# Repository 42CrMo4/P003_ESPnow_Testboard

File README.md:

# ESPnow Testboard

Quick first shot for an ESP32-C3 based ESPnow communication PCB 

## Description. 

|     Font      |     Back      |
| ------------- | ------------- |
|||

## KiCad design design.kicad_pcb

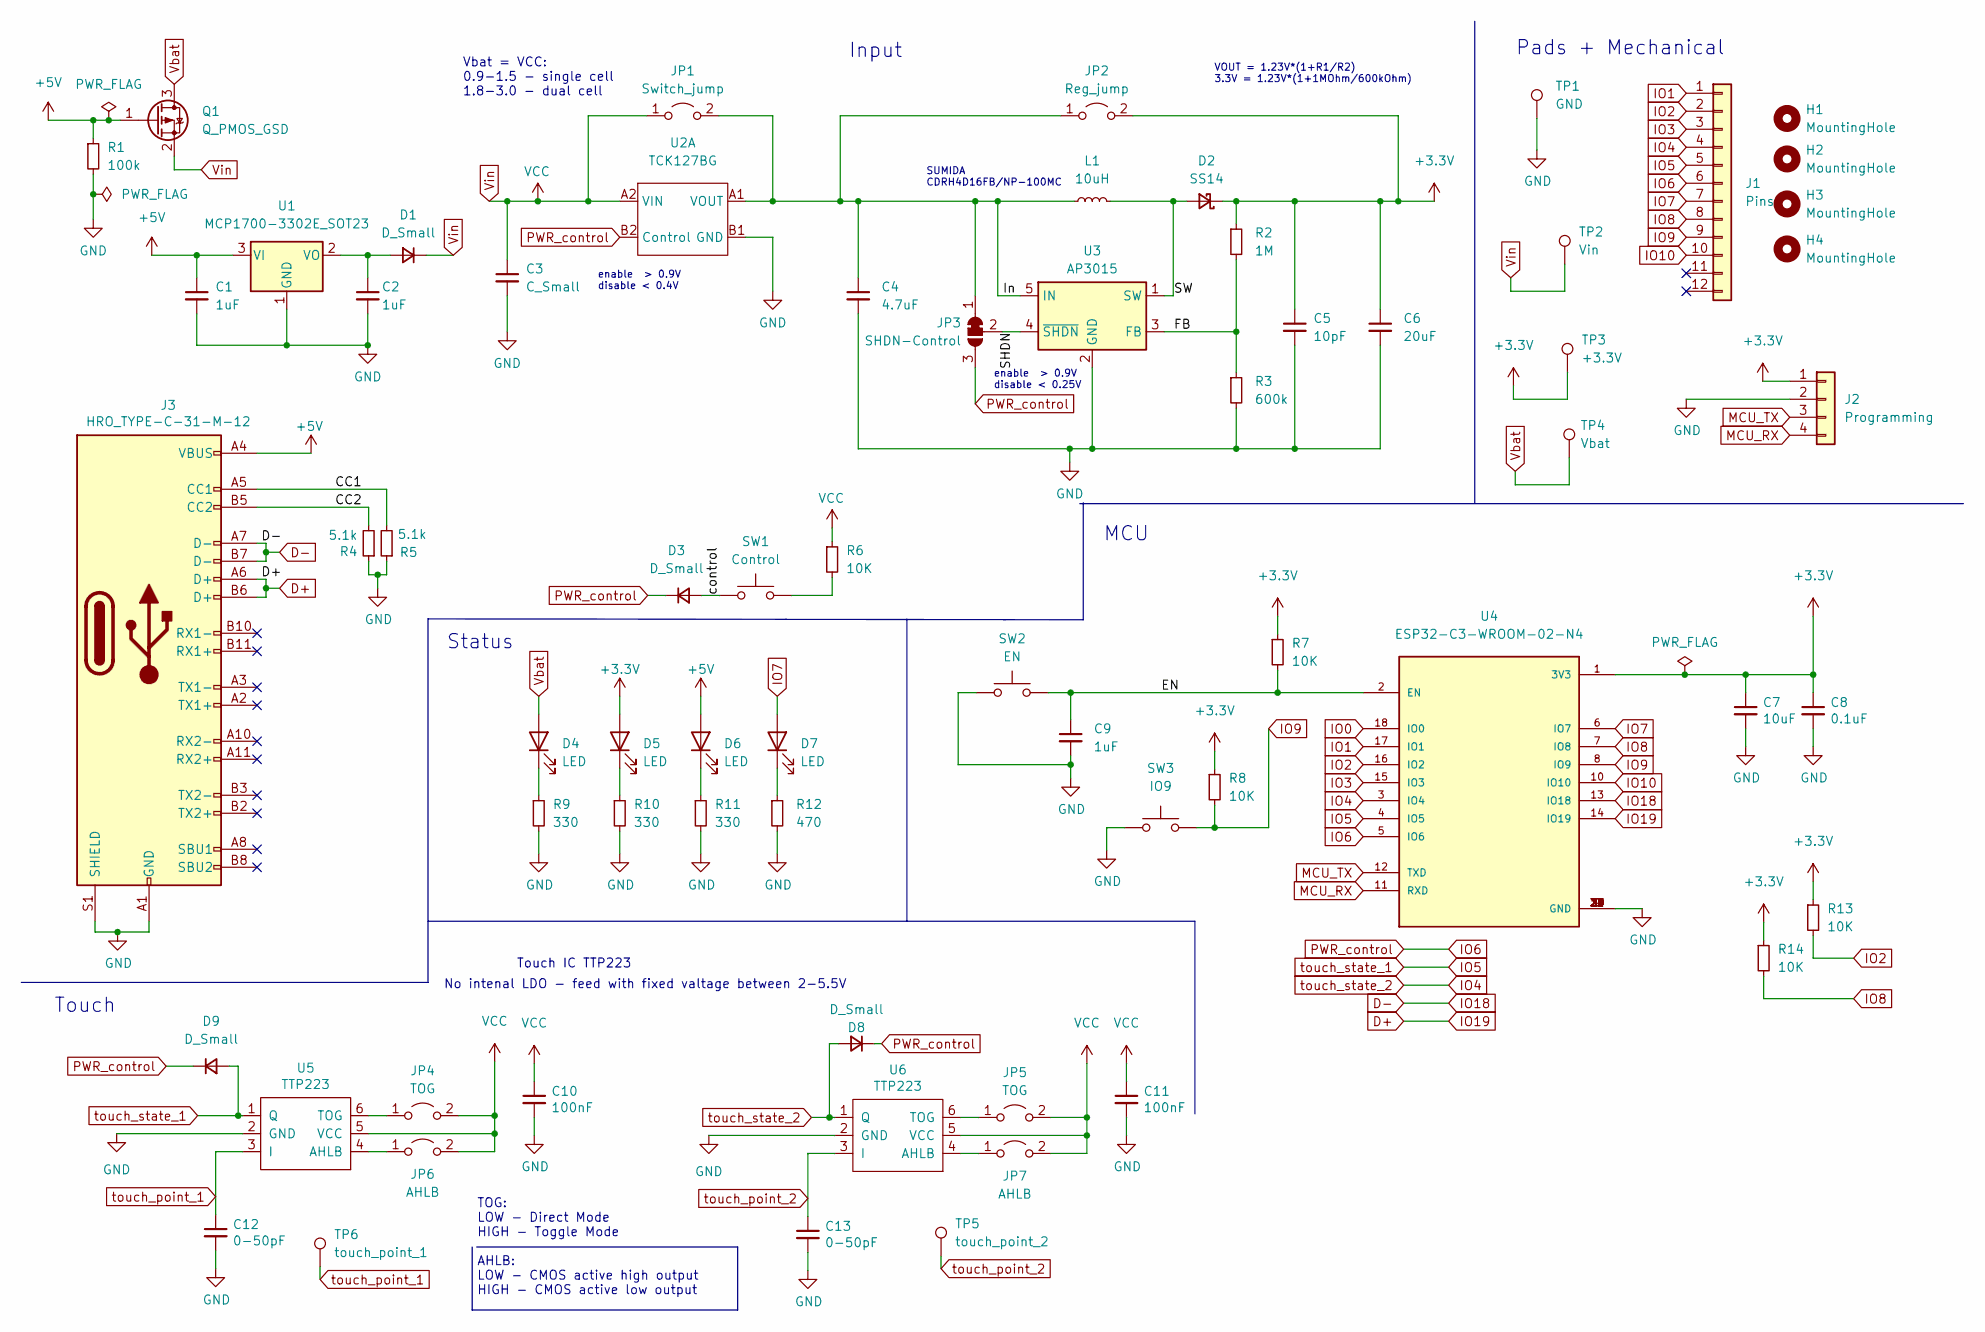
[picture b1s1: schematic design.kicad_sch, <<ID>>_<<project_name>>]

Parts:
C1, C2, C9: 1uF; C_0805_2012Metric
C3: C_Small; C_0805_2012Metric
C4: 4.7uF; C_0805_2012Metric
C5: 10pF; C_0805_2012Metric
C6: 20uF; C_0805_2012Metric
C7: 10uF; C_0805_2012Metric
C8: 0.1uF; C_0805_2012Metric
C10, C11: 100nF; C_0805_2012Metric
C12, C13: 0-50pF; C_0805_2012Metric
D1, D3, D8, D9: D_Small; D_SOD-323
D2: SS14; D_SMA
D4, D5, D6, D7: LED; LED_0603_1608Metric
H1, H2, H3, H4: MountingHole; MountingHole_3.2mm_M3_Pad_Via
J1: Pins; PinSocket_2x06_P2.54mm_Vertical_SMD
J2: Programming; PinHeader_1x04_P2.54mm_Vertical
J3: HRO_TYPE-C-31-M-12; USB_C_Receptacle_HRO_TYPE-C-31-M-12
JP1: Switch_jump; SolderJumper-2_P1.3mm_Open_RoundedPad1.0x1.5mm
JP2: Reg_jump; SolderJumper-2_P1.3mm_Open_RoundedPad1.0x1.5mm
JP3: SHDN-Control; SolderJumper-3_P1.3mm_Bridged12_RoundedPad1.0x1.5mm_NumberL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
JP4, JP5: TOG; SolderJumper-2_P1.3mm_Open_RoundedPad1.0x1.5mm
JP6, JP7: AHLB; SolderJumper-2_P1.3mm_Open_RoundedPad1.0x1.5mm
L1: 10uH; L_TracoPower_TCK-047_5.2x5.8mm
Q1: Q_PMOS_GSD; SOT-23
R1: 100k; R_0805_2012Metric
R2: 1M; R_0805_2012Metric
R3: 600k; R_0805_2012Metric
R4, R5: 5.1k; R_0805_2012Metric
R6, R7, R8, R13, R14: 10K; R_0805_2012Metric
R9, R10, R11: 330; R_0805_2012Metric
R12: 470; R_0805_2012Metric
SW1: Control; SW_SPST_EVPBF
SW2: EN; SW_SPST_EVPBF
SW3: IO9; SW_SPST_EVPBF
TP1: GND; TestPoint_Pad_D2.5mm
TP2: Vin; TestPoint_Pad_D2.5mm
TP3: +3.3V; TestPoint_Pad_D2.5mm
TP4: Vbat; TestPoint_Pad_D2.5mm
TP5: touch_point_2
TP6: touch_point_1
U1: MCP1700-3302E_SOT23; SOT-23
U2: TCK127BG; Toshiba_WCSP4G
U3: AP3015; SOT-23-5
U4: ESP32-C3-WROOM-02-N4; MODULE_ESP32-C3-WROOM-02-H4
U5, U6: TTP223; SOT-23-6_Handsoldering

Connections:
+3.3V: C5.1, C6.1, C7.1, C8.1, D2.1 (K), D5.2 (A), J2.1, JP2.2 (B), R2.1, R7.1, R8.1, R13.1, R14.1, TP3.1, U4.1 (3V3)
+5V: C1.1, D6.2 (A), J3.A4 (VBUS), J3.A9 (VBUS), J3.B4 (VBUS), J3.B9 (VBUS), Q1.1 (G), R1.1, U1.3 (VI)
/CC1: J3.A5 (CC1), R5.2
/CC2: J3.B5 (CC2), R4.2
/EN: C9.1, R7.2, SW2.2, U4.2 (EN)
/FB: R2.2, R3.1, U3.3 (FB)
/In: C4.1, JP1.2 (B), JP2.1 (A), JP3.1 (A), L1.1, U2.A1 (VOUT), U3.5 (IN)
/SHDN: JP3.2 (C), U3.4 (~SHDN)
/SW: D2.2 (A), L1.2, U3.1 (SW)
/control: D3.2 (A), SW1.1
D+: J3.A6 (D+), J3.B6 (D+), U4.14 (IO19)
D-: J3.A7 (D-), J3.B7 (D-), U4.13 (IO18)
GND: C1.2, C2.2, C3.2, C4.2, C5.2, C6.2, C7.2, C8.2, C9.2, C10.2, C11.2, C12.2, C13.2, J2.2, J3.A1 (GND), J3.A12 (GND), J3.B1 (GND), J3.B12 (GND), J3.S1 (SHIELD), R1.2, R3.2, R4.1, R5.1, R9.2, R10.2, R11.2, R12.2, SW2.1, SW3.1, TP1.1, U1.1 (GND), U2.B1 (GND), U3.2 (GND), U4.9 (GND), U4.19 (GND), U4.20 (GND), U4.21 (GND), U4.22 (GND), U4.23 (GND), U4.24 (GND), U4.25 (GND), U4.26 (GND), U4.27 (GND), U4.28 (GND), U4.29 (GND), U4.30 (GND), U4.31 (GND), U4.32 (GND), U4.33 (GND), U4.34 (GND), U4.35 (GND), U4.36 (GND), U4.37 (GND), U4.38 (GND), U4.39 (GND), U5.2 (GND), U6.2 (GND)
IO0: U4.18 (IO0)
IO1: J1.1, U4.17 (IO1)
IO2: J1.2, R13.2, U4.16 (IO2)
IO3: J1.3, U4.15 (IO3)
IO4: D8.2 (A), J1.4, U4.3 (IO4), U6.1 (Q)
IO5: D9.2 (A), J1.5, U4.4 (IO5), U5.1 (Q)
IO6: D3.1 (K), D8.1 (K), D9.1 (K), J1.6, JP3.3 (B), U2.B2 (Control), U4.5 (IO6)
IO7: D7.2 (A), J1.7, U4.6 (IO7)
IO8: J1.8, R14.2, U4.7 (IO8)
IO9: J1.9, R8.2, SW3.2, U4.8 (IO9)
IO10: J1.10, U4.10 (IO10)
MCU_RX: J2.4, U4.11 (RXD)
MCU_TX: J2.3, U4.12 (TXD)
unnamed: C2.1, D1.2 (A), U1.2 (VO)
unnamed: D4.1 (K), R9.1
unnamed: D5.1 (K), R10.1
unnamed: D6.1 (K), R11.1
unnamed: D7.1 (K), R12.1
unnamed: JP4.1 (A), U5.6 (TOG)
unnamed: JP5.1 (A), U6.6 (TOG)
unnamed: JP6.1 (A), U5.4 (AHLB)
unnamed: JP7.1 (A), U6.4 (AHLB)
unnamed: R6.2, SW1.2
Vbat: D4.2 (A), Q1.3 (D), TP4.1
Vin: C3.1, C10.1, C11.1, D1.1 (K), JP1.1 (A), JP4.2 (B), JP5.2 (B), JP6.2 (B), JP7.2 (B), Q1.2 (S), R6.1, TP2.1, U2.A2 (VIN), U5.5 (VCC), U6.5 (VCC)
touch_point_1: C12.1, TP6.1, U5.3 (I)
touch_point_2: C13.1, TP5.1, U6.3 (I)

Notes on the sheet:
enable > 0.9V disable < 0.25V
Pads + Mechanical
enable > 0.9V disable < 0.4V
SUMIDA CDRH4D16FB/NP-100MC
Touch IC TTP223
No intenal LDO - feed with fixed valtage between 2-5.5V
Vbat = VCC: 0.9-1.5 - single cell 1.8-3.0 - dual cell
VOUT = 1.23V*(1+R1/R2) 3.3V = 1.23V*(1+1MOhm/600kOhm)
Status
TOG: LOW - Direct Mode HIGH - Toggle Mode AHLB: LOW - CMOS active high output HIGH - CMOS active low output
Input
Touch
MCU

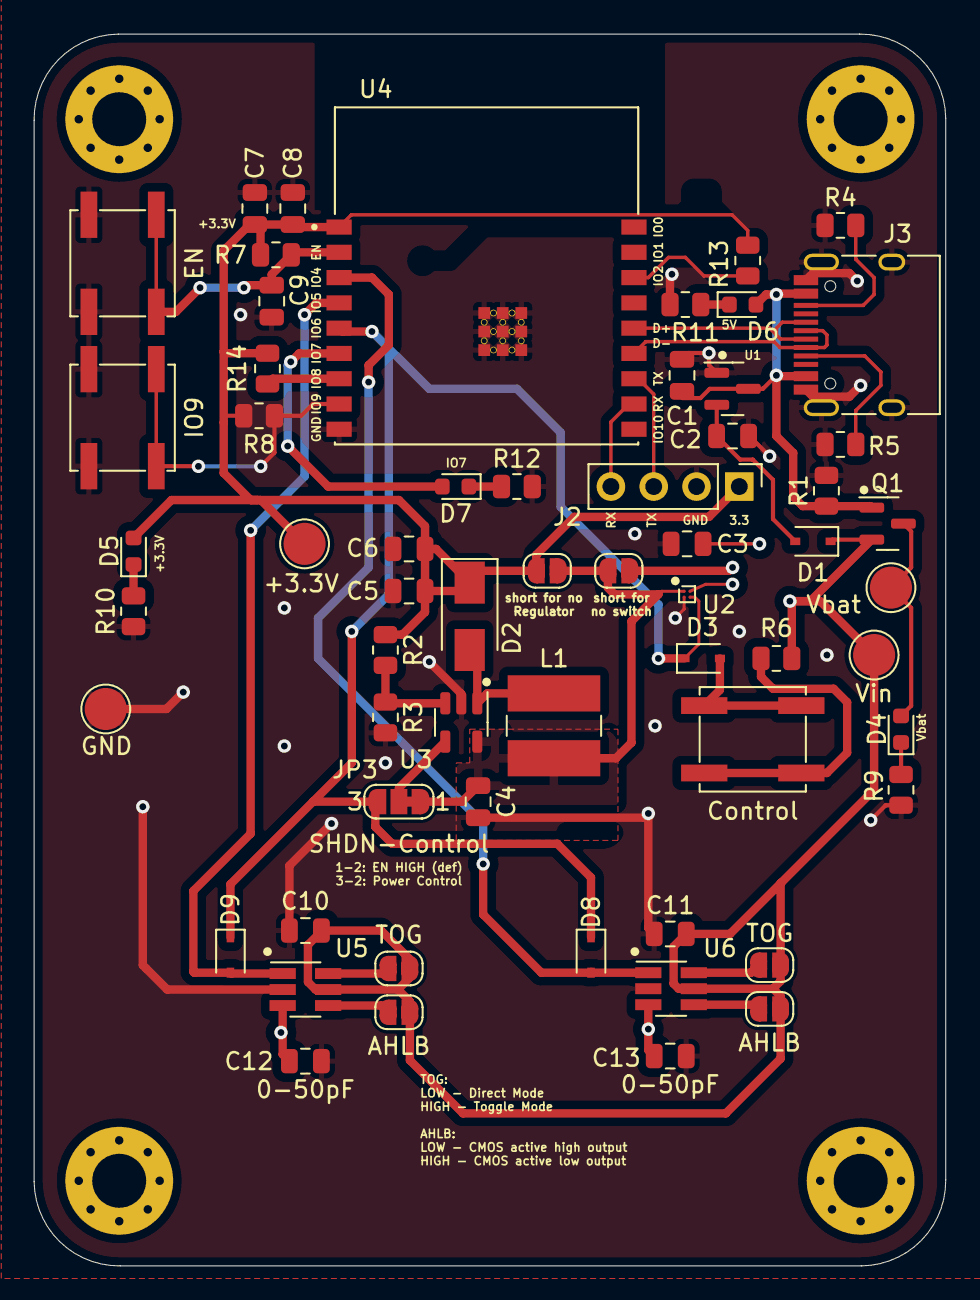
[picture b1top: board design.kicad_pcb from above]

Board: 2 copper layers, 54.1 x 73.1 mm, 64 parts (0 on the bottom side), 36 nets.

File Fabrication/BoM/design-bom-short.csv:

Row,Description,Part,References,Value,Footprint,Quantity Per PCB,Status,Datasheet,MF,AVAILABILITY,PRICE,PACKAGE,MP,PURCHASE-URL
1,"Unpolarized capacitor, small symbol",C_Small,C5,10pF,C_0805_2012Metric,1, ,~,,,,,,
2,"Unpolarized capacitor, small symbol",C_Small,C8 C10 C11,0.1uF,C_0805_2012Metric,3, ,~,,,,,,
3,"Unpolarized capacitor, small symbol",C_Small,C1 C2 C9,1uF,C_0805_2012Metric,3, ,~,,,,,,
4,"Unpolarized capacitor, small symbol",C_Small,C4,4.7uF,C_0805_2012Metric,1, ,~,,,,,,
5,"Unpolarized capacitor, small symbol",C_Small,C7,10uF,C_0805_2012Metric,1, ,~,,,,,,
6,"Unpolarized capacitor, small symbol",C_Small,C6,20uF,C_0805_2012Metric,1, ,~,,,,,,
7,"Unpolarized capacitor, small symbol",C_Small,C12 C13,0-50pF,C_0805_2012Metric,2, ,~,,,,,,
8,"Unpolarized capacitor, small symbol",C_Small,C3,C_Small,C_0805_2012Metric,1, ,~,,,,,,
9,"Diode, small symbol",D_Small,D1 D3 D8 D9,D_Small,D_SOD-323,4, ,~,,,,,,
10,Light emitting diode,LED,D4 D5 D6 D7,LED,LED_0603_1608Metric,4, ,~,,,,,,
11,"Schottky diode, small symbol",D_Schottky_Small,D2,SS14,D_SMA,1, ,~,,,,,,
12,USB Full-Featured Type-C Receptacle connector,USB_C_Receptacle,J3,HRO_TYPE-C-31-M-12,USB_C_Receptacle_HRO_TYPE-C-31-M-12,1, ,https://www.usb.org/sites/default/files/documents/usb_type-c.zip,,,,,,
13,"Generic connector, single row, 01x12, script generated (kicad-library-utils/schlib/autogen/connector/)",Conn_01x12,J1,Pins,PinSocket_2x06_P2.54mm_Vertical_SMD,1, ,~,,,,,,
14,"Generic connector, single row, 01x04, script generated (kicad-library-utils/schlib/autogen/connector/)",Conn_01x04,J2,Programming,PinHeader_1x04_P2.54mm_Vertical,1, ,~,,,,,,
15,"Jumper, 2-pole, open",Jumper_2_Open,JP6 JP7,AHLB,SolderJumper-2_P1.3mm_Open_RoundedPad1.0x1.5mm,2, ,~,,,,,,
16,"Jumper, 2-pole, open",Jumper_2_Open,JP2,Reg_jump,SolderJumper-2_P1.3mm_Open_RoundedPad1.0x1.5mm,1, ,~,,,,,,
17,"Jumper, 2-pole, open",Jumper_2_Open,JP1,Switch_jump,SolderJumper-2_P1.3mm_Open_RoundedPad1.0x1.5mm,1, ,~,,,,,,
18,"Jumper, 2-pole, open",Jumper_2_Open,JP4 JP5,TOG,SolderJumper-2_P1.3mm_Open_RoundedPad1.0x1.5mm,2, ,~,,,,,,
19,"Inductor, small symbol",L_Small,L1,10uH,L_TracoPower_TCK-047_5.2x5.8mm,1, ,~,,,,,,
20,"P-MOSFET transistor, gate/source/drain",Q_PMOS_GSD,Q1,Q_PMOS_GSD,SOT-23,1, ,~,,,,,,
21,"Resistor, small symbol",R_Small,R9 R10 R11,330,R_0805_2012Metric,3, ,~,,,,,,
22,"Resistor, small symbol",R_Small,R12,470,R_0805_2012Metric,1, ,~,,,,,,
23,"Resistor, small symbol",R_Small,R4 R5,5.1k,R_0805_2012Metric,2, ,~,,,,,,
24,"Resistor, small symbol",R_Small,R6 R7 R8 R13 R14,10K,R_0805_2012Metric,5, ,~,,,,,,
25,"Resistor, small symbol",R_Small,R1,100k,R_0805_2012Metric,1, ,~,,,,,,
26,"Resistor, small symbol",R_Small,R3,600k,R_0805_2012Metric,1, ,~,,,,,,
27,"Resistor, small symbol",R_Small,R2,1M,R_0805_2012Metric,1, ,~,,,,,,
28,"Push button switch, generic, two pins",SW_Push,SW1,Control,SW_SPST_EVPBF,1, ,~,,,,,,
29,"Push button switch, generic, two pins",SW_Push,SW2,EN,SW_SPST_EVPBF,1, ,~,,,,,,
30,"Push button switch, generic, two pins",SW_Push,SW3,IO9,SW_SPST_EVPBF,1, ,~,,,,,,
31,"500mA, Adjustable Step-Up Voltage Regulator, 1.5MHz Frequency, SOT-23-5",AP3012,U3,AP3015,SOT-23-5,1, ,https://www.diodes.com/assets/Datasheets/AP3012.pdf,,,,,,
32,"WiFi Modules (802.11) (Engineering Samples) SMD module, ESP32-C3, 4MB SPI flash, PCB antenna, -40 C +105 C",ESP32-C3-WROOM-02-N4,U4,ESP32-C3-WROOM-02-N4,MODULE_ESP32-C3-WROOM-02-H4,1, ,,Espressif Systems,In Stock,None,Package,ESP32-C3-WROOM-02-H4,https://pricing.snapeda.com/search/part/ESP32-C3-WROOM-02-H4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
33,"250mA Low Quiscent Current LDO, 3.3V output, SOT-23",MCP1700-3302E_SOT23,U1,MCP1700-3302E_SOT23,SOT-23,1, ,http://ww1.microchip.com/downloads/en/DeviceDoc/20001826D.pdf,,,,,,
34,,"TCK127BG,LF",U2,TCK127BG,Toshiba_WCSP4G,1, ,https://toshiba.semicon-storage.com/info/TCK127BG_datasheet_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,,,,,,
35,,TTP223,U5 U6,TTP223,SOT-23-6_Handsoldering,2, ,,,,,,,

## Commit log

2022-10-20 DEL all template stuff
2022-10-20 ADD properties
2022-10-20 ADD autosafe file to gitignore
2022-10-20 SCH Add initial design
2022-10-20 test if bom ist problem
2022-10-26 Revert "Update generate_output.yml"
    This reverts commit a08b70d7cc8388dabf49793725c9e2c4a6bce6b5.
2022-10-26 Revert "Delete design.kicad_prl"
    This reverts commit b7ddf9ab9ad1b30fd9299fe4ec3c922bd4cd57f0.
2022-10-26 Revert "Delete design-cache.lib"
    This reverts commit b4e336c11d0fae9e2be307904ffc91d158592678.
2022-10-26 Revert "Delete design-cache.lib"
    This reverts commit 448950eb7e596fc9faa64de86c6f8c44a2f9cfd1.
2022-10-26 Update to Kibot 1.4.0 (#1)
    * Update generate_output.yml
2022-10-26 Delete unneeded kicad files (#2)
    * Delete design-cache.lib
    * Delete design.kicad_prl
2022-10-26 Diff only with KIBOT_LAST-1, rename action
2022-10-26 Update Bom and PCB_top
2022-10-26 Diff only with KIBOT_LAST-1, rename action (#3)
    * Diff only with KIBOT_LAST-1, rename action
    * Update Bom and PCB_top
2022-10-26 Fixed Project name Whitespace
    The project name is not allowed to have a whitespace in the name as this is a problem in the shell scripts of the workflow.
2022-10-26 Project name whitespace problme (#4)
    * Fixed Project name Whitespace
    The project name is not allowed to have a whitespace in the name as this is a problem in the shell scripts of the workflow.
    * Update generate_output.yml
2022-10-26 enable iBOM action
2022-10-26 add footprints
2022-10-26 PCB outline
2022-10-26 iBom fix (#5)
    * enable iBOM action
    * add footprints
    * Update design.kicad_pcb
    * Update design.kicad_sch
    * PCB outline
2022-10-28 repair schematic after git collision
2022-10-28 removed last line
2022-11-06 PCB scramble
2022-11-06 Kiplot zoom step
2022-11-14 cleaning up
    silkscreen
    info text
    description
    adding warning about unfinished input voltage rail
2022-11-16 Add USB to 3.3V and powerpath USB/Vbat
2022-11-18 checklist + final touchup SCH/PCB
2022-11-18 rounded corners + mounting holes with copper
    closes #7
2022-11-19 move silksreen add clearance to m3 mounting pads
2022-11-26 PCB: move silk screen
2022-11-26 Finish Checklist
2022-11-27 PCB small silkscreen move
2022-11-27 Archive & Renew release docs
2022-12-21 pin IO9 connect to push button instead of IO0
2022-12-21 pin IO9 connect to push button instead of IO0 (#11)
    * pin IO9 connect to push button instead of IO0
2022-12-21 use 3.6V regulator
    because of voltage drop on Diode
    closes #10
2022-12-29 Add the correct AP3015 Datasheet to SCH Symbol
